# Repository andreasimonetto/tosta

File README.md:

# Tosta

Tosta is a **low-power terminal interface module** built around the [STM32G030](docs/STM32G0x0.pdf) microcontroller. The module features:

- 48x84 monochrome pixel matrix (Nokia 5510 LCD using [PCD8544](docs/PCD8544.pdf) controller)
- configurable dimmable backlight
- configurable display standby timer
- a rotary encoder with central switch
- a D-Pad joystick with central switch
- 4 tactile switches
- a speaker
- an UART interface @ 115200 baud/s
- an I2C slave interface @ 400KHz (address 0x7D)
- 150uA consumption in standby mode

## User guide

The main communication interface (characters based) is UART @ 115200 baud/s.
I2C (binary based) is used for fast display update among other things.

### UART Inputs

When the module receive an input, it send a corresponding command character as
follows:

Event                        | Hex  | Char
---------------------------- | ---- | ----
SW1 pressed                  | 0x41 | A
SW1 released                 | 0x61 | a
SW2 pressed                  | 0x42 | B
SW2 released                 | 0x62 | b
SW3 pressed                  | 0x43 | C
SW3 released                 | 0x63 | c
SW4 pressed                  | 0x44 | D
SW4 released                 | 0x64 | d
D-Pad button pressed         | 0x45 | E
D-Pad button released        | 0x65 | e
D-Pad left pressed           | 0x46 | F
D-Pad left released          | 0x66 | f
D-Pad right pressed          | 0x47 | G
D-Pad right released         | 0x67 | g
D-Pad up pressed             | 0x48 | H
D-Pad up released            | 0x68 | h
D-Pad down pressed           | 0x49 | I
D-Pad down released          | 0x69 | i
Encoder button pressed       | 0x4A | J
Encoder button released      | 0x6A | j
Encoder turn clockwise       | 0x2B | +
Encoder turn anti-clockwise  | 0x2D | -

### Display matrix

The display matrix comprises 84 horizontal by 48 vertical pixels.
Each individual pixel is either *on* (1) or *off* (0) which corresponds to the
status of a single bit. Individual bits are grouped into bytes, representing
a sub-column of 8 pixels.

The next byte is the nearby sub-column, on the right side. The display
frame buffer contains a total 504 bytes: 84 for the upper sub-columns, 84 for
the next ones and so on, for a total of 6 (84x6 bytes, row-major ordering).

Characters are a logical subdivision into a 14x6 matrix, in which each cell is
a 6x8 pixels sub-matrix (see blue lines).

```
h   0x7f 0x08 0x04 0x04 0x78 0x00
e   0x38 0x54 0x54 0x54 0x18 0x00
l   0x00 0x41 0x7f 0x40 0x00 0x00
l   0x00 0x41 0x7f 0x40 0x00 0x00
o   0x38 0x44 0x44 0x44 0x38 0x00
!   0x00 0x00 0x5f 0x00 0x00 0x00
```

### UART outputs

Writing characters works as usual on a *tty* device, using standard ASCII
encoding (printable characters from 0x20 up to 0x7F). There are few special
characters:

- `\a` (bell): play a C4 note from the speaker for 250ms
- `\b` (backspace): delete the last displayed character
- `\n` (line feed): newline
- `\f` (form feed): clear screen
- `\r` (carriage return): move cursor to the beginning of the current line

The user can also add non-standard custom characters (from 0x80 to 0xFF) using
[parametric escape sequences](#escape-sequences).

#### Escape sequences

Escape sequences are used to obtain special behaviours. In order to start
an escape sequence, the special character `\e` (or `\x1B` or `\033`) must be
used.

Basic sequences are:

Sequence | Effect
-------- | ---------------------------------
`\es`    | Put the display in standby
`\ew`    | Wake up the display from standby
`\el`    | Display an awesome logo

Advanced sequences allow passing numerical parameters, and they're started
using `\e[` (i.e. `\x1B[` or `\033[`).

Sequence                           | Effect
-----------------                  | ------------------------------------------------------------
`\e[`N`b`                          | Set display backlight brightness, with *N in [0, 127]*
`\e[`N`,`A`,`B`,`C`,`D`,`E`,`F`c`  | Set user character *N*, specifying bytes in the character sub-matrix from left to right (*N in [128, 255]*; *A,B,C,D,E,F in [0, 255])*
`\e[`F`,`T`p`                      | Play sound (immediate) having frequency *F* for *T* milliseconds
`\e[`F`,`T`q`                      | Enqueue sound playing with frequency *F* for *T* milliseconds
`\e[`T`s`                          | Set the display standby timer in *T* milliseconds (0 to disable standby)
`\e[`X`,`Y`z`                      | Set cursor position to *X in [0, 13]* and *Y in [0, 5]*

##### Example

```sh
stty -F /dev/ttyUSB0 115200
echo -ne "\e[128,12,30,60,30,12,0c" >>/dev/ttyUSB0
echo -ne "\f\x80\x80\x80\x80\x80\x80\x80\x80\x80\x80\x80\x80\x80\x80Frere Jacques\n\x80\x80\x80\x80\x80\x80\x80\x80\x80\x80\x80\x80\x80\x80" >>/dev/ttyUSB0
echo -ne "\e[1047,500q\e[1175,500q\e[1319,500q\e[1047,500q\e[1047,500q\e[1175,500q\e[1319,500q\e[1047,500q\e[1319,500q\e[1397,500q\e[1568,500q\e[0,500q\e[1319,500q\e[1397,500q\e[1568,500q" >>/dev/ttyUSB0
```

### I²C

- Send 1 byte to address 0x7D for command (0), necessary to wake the MCU from stop mode nicely
- Send the framebuffer (504 bytes) to address 0x7D
- ...

## Firmware

Firmware is written using the [STM32 Cube IDE](https://www.st.com/en/development-tools/stm32cubeide.html).

### Peripherals assignment:

- TIM1: speaker PWM
- TIM3: LCD backlight PWM
- TIM14: Inputs debounce
- SPI1+DMA: LCD data output
- UART: main serial communication interface
- I2C1: secondary communication interface (slave)

## Hardware

## Trivia

```C
0x7D == ('t' ^ 'o' ^ 's' ^ 't' ^ 'a')
```

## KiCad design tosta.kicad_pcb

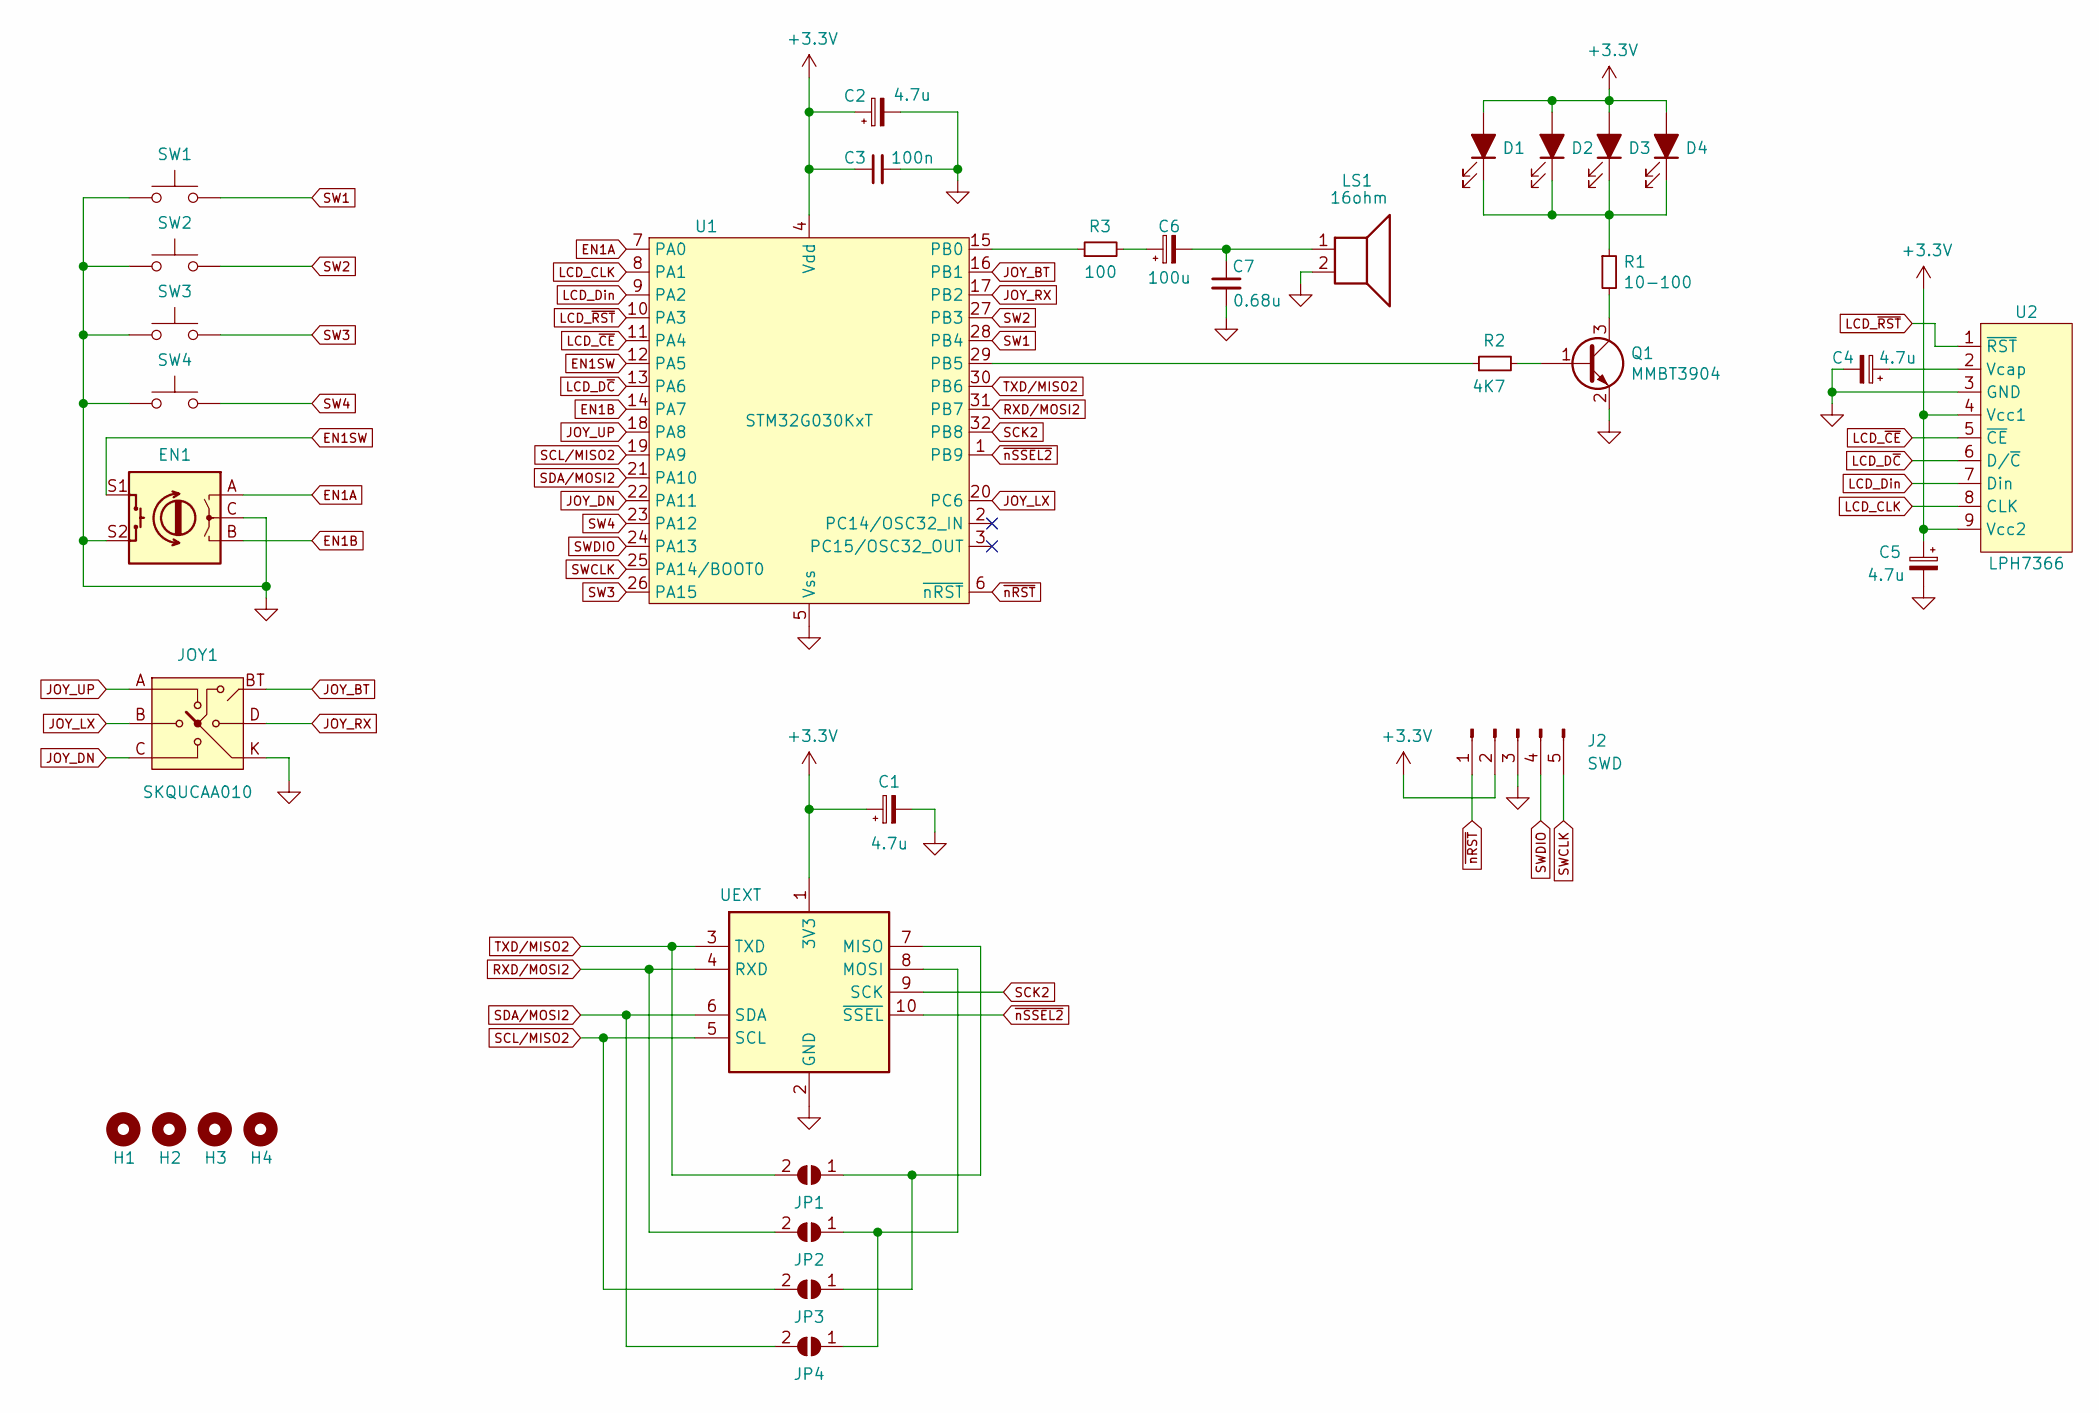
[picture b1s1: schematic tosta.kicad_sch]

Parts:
C1, C2, C4, C5: 4.7u; CP_EIA-3216-12_Kemet-S_Pad1.58x1.35mm_HandSolder
C3: 100n; C_0805_2012Metric_Pad1.15x1.40mm_HandSolder
C6: 100u; CP_EIA-3216-12_Kemet-S_Pad1.58x1.35mm_HandSolder
C7: 0.68u; C_0805_2012Metric_Pad1.18x1.45mm_HandSolder
D1, D2, D3, D4: LED_ALT; LED_0805_2012Metric
EN1: Rotary_Encoder_Switch; RotaryEncoder_Alps_EC12E-Switch_Vertical_H20mm
H1, H2, H3, H4: MountingHole; M3_ISO7380
J2: SWD; PinHeader_1x05_P2.54mm_Vertical
JOY1: SKQUCAA010
JP1, JP2, JP3, JP4: SolderJumper_2_Open; SolderJumper-2_P1.3mm_Open_RoundedPad1.0x1.5mm
LS1: 16ohm; KY_BUZ
Q1: MMBT3904; SOT-23
R1: 10-100; R_0805_2012Metric_Pad1.15x1.40mm_HandSolder
R2: 4K7; R_0805_2012Metric_Pad1.15x1.40mm_HandSolder
R3: 100; R_0805_2012Metric_Pad1.20x1.40mm_HandSolder
SW1, SW2, SW3, SW4: SW_Push; SW_PUSH_6mm_H4.3mm
U1: STM32G030KxT; LQFP-32_7x7mm_P0.8mm
U2: LPH7366
UEXT: UEXT; IDC-Header_2x05_P2.54mm_Vertical

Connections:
+3V3: C1.1, C2.1, C3.1, C5.1, D1.2 (A), D2.2 (A), D3.2 (A), D4.2 (A), J2.2, U1.4 (Vdd), U2.4 (Vcc1), U2.9 (Vcc2), UEXT.1 (3V3)
EN1A: EN1.A, U1.7 (PA0)
EN1B: EN1.B, U1.14 (PA7)
EN1SW: EN1.S1, U1.12 (PA5)
GND: C1.2, C2.2, C3.2, C4.2, C5.2, C7.2, EN1.C, EN1.S2, J2.3, JOY1.K, LS1.2, Q1.2 (E), SW1.2, SW2.2, SW3.2, SW4.2, U1.5 (Vss), U2.3 (GND), UEXT.2 (GND)
JOY_BT: JOY1.BT, U1.16 (PB1)
JOY_DN: JOY1.C, U1.22 (PA11)
JOY_LX: JOY1.B, U1.20 (PC6)
JOY_RX: JOY1.D, U1.17 (PB2)
JOY_UP: JOY1.A, U1.18 (PA8)
LCD_CLK: U1.8 (PA1), U2.8 (CLK)
LCD_Din: U1.9 (PA2), U2.7 (Din)
LCD_D~C: U1.13 (PA6), U2.6 (D/~C)
LCD_~CE: U1.11 (PA4), U2.5 (~CE)
LCD_~RST: U1.10 (PA3), U2.1 (~RST)
unnamed: C4.1, U2.2 (Vcap)
unnamed: C6.1, R3.2
unnamed: C6.2, C7.1, LS1.1
unnamed: D1.1 (K), D2.1 (K), D3.1 (K), D4.1 (K), R1.1
unnamed: JP1.1 (A), JP3.1 (A), UEXT.7 (MISO)
unnamed: JP2.1 (A), JP4.1 (A), UEXT.8 (MOSI)
unnamed: Q1.1 (B), R2.2
unnamed: Q1.3 (C), R1.2
unnamed: R2.1, U1.29 (PB5)
unnamed: R3.1, U1.15 (PB0)
RXD/MOSI2: JP2.2 (B), U1.31 (PB7), UEXT.4 (RXD)
SCK2: U1.32 (PB8), UEXT.9 (SCK)
SCL/MISO2: JP3.2 (B), U1.19 (PA9), UEXT.5 (SCL)
SDA/MOSI2: JP4.2 (B), U1.21 (PA10), UEXT.6 (SDA)
SW1: SW1.1, U1.28 (PB4)
SW2: SW2.1, U1.27 (PB3)
SW3: SW3.1, U1.26 (PA15)
SW4: SW4.1, U1.23 (PA12)
SWCLK: J2.5, U1.25 (PA14/BOOT0)
SWDIO: J2.4, U1.24 (PA13)
TXD/MISO2: JP1.2 (B), U1.30 (PB6), UEXT.3 (TXD)
~nRST: J2.1, U1.6 (~nRST)
~nSSEL2: U1.1 (PB9), UEXT.10 (~SSEL)

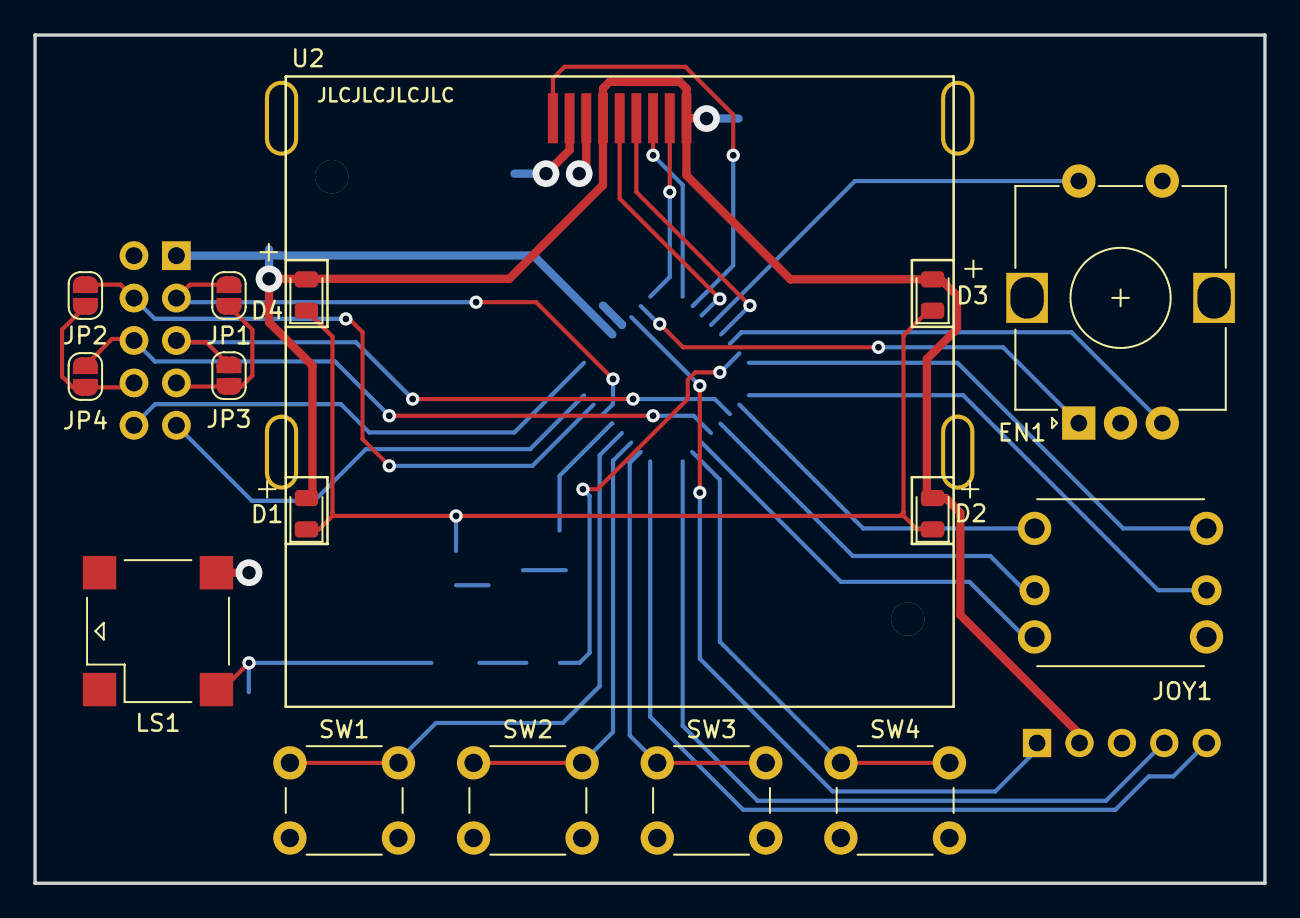
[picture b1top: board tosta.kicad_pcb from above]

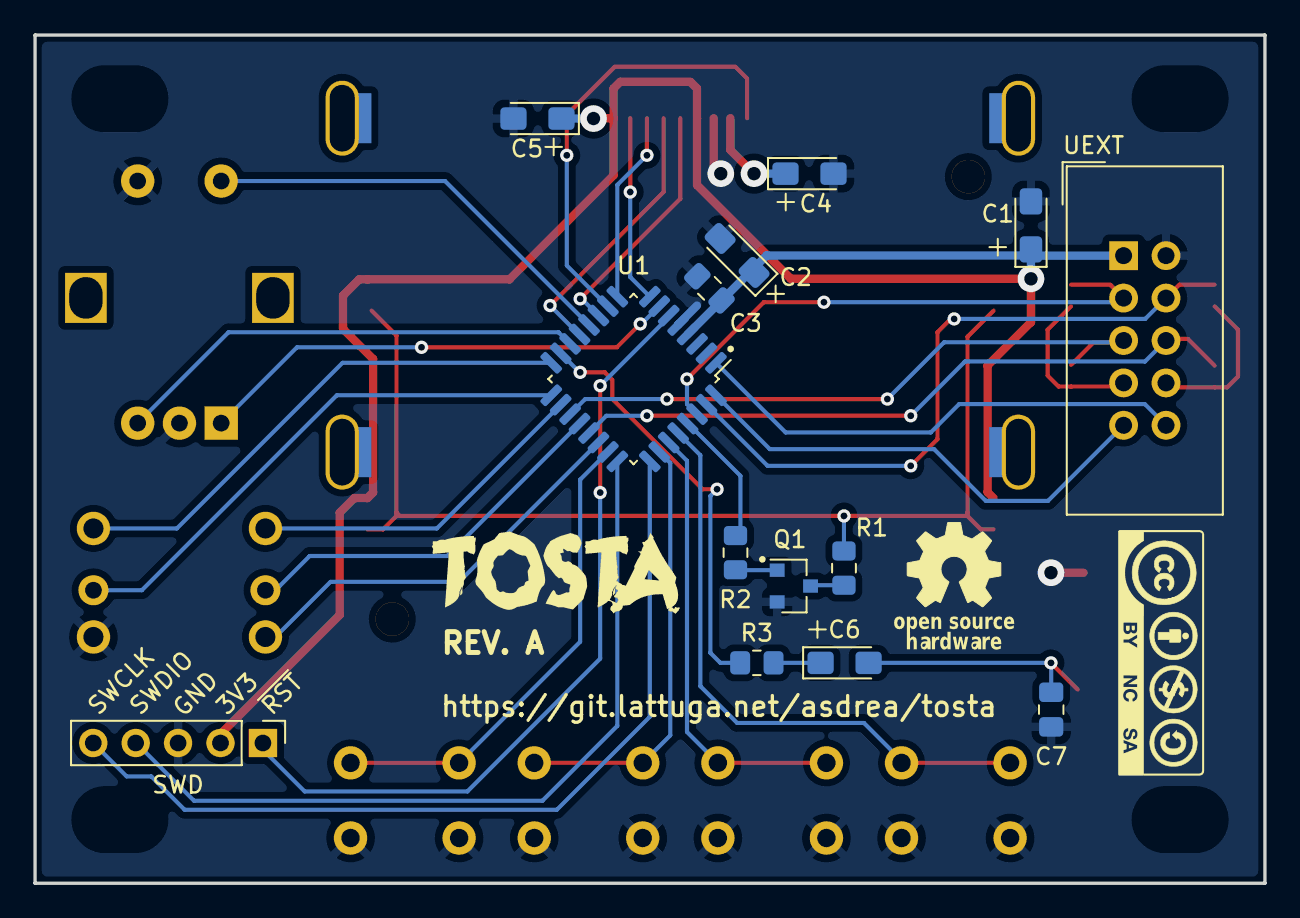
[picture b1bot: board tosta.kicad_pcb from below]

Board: 2 copper layers, 73.7 x 50.8 mm, 37 parts (17 on the bottom side), 38 nets.

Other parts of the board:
CC_BYNCSA: G***; cc_byncsa
OSHW: G***; oshw
svg2mod: G***; logo

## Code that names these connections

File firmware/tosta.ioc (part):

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Mcu.Name=STM32G030K(6-8)Tx
Mcu.Package=LQFP32
Mcu.UserName=STM32G030K6Tx
PA0.GPIOParameters=GPIO_PuPd,GPIO_Label,GPIO_ModeDefaultEXTI
PA0.GPIO_Label=EN1A
PA0.GPIO_ModeDefaultEXTI=GPIO_MODE_IT_RISING_FALLING
PA0.GPIO_PuPd=GPIO_PULLUP
PA0.Signal=GPXTI0
PA1.GPIOParameters=GPIO_Speed,GPIO_Label
PA1.GPIO_Label=LCD_CLK
PA1.GPIO_Speed=GPIO_SPEED_FREQ_HIGH
PA1.Mode=TX_Only_Simplex_Unidirect_Master
PA1.Signal=SPI1_SCK
PA10.GPIOParameters=GPIO_PuPdOD,GPIO_Label
PA10.GPIO_Label=SDA
PA10.GPIO_PuPdOD=GPIO_NOPULL
PA10.Mode=I2C
PA10.Signal=I2C1_SDA
PA11\ [PA9].GPIOParameters=GPIO_PuPd,GPIO_Label,GPIO_ModeDefaultEXTI
PA11\ [PA9].GPIO_Label=JOY_DN
PA11\ [PA9].GPIO_ModeDefaultEXTI=GPIO_MODE_IT_RISING_FALLING
PA11\ [PA9].GPIO_PuPd=GPIO_PULLUP
PA11\ [PA9].Signal=GPXTI11
PA12\ [PA10].GPIOParameters=GPIO_PuPd,GPIO_Label,GPIO_ModeDefaultEXTI
PA12\ [PA10].GPIO_Label=SW4
PA12\ [PA10].GPIO_ModeDefaultEXTI=GPIO_MODE_IT_RISING_FALLING
PA12\ [PA10].GPIO_PuPd=GPIO_PULLUP
PA12\ [PA10].Signal=GPXTI12
PA13.Mode=Serial_Wire
PA13.Signal=SYS_SWDIO
PA14-BOOT0.Mode=Serial_Wire
PA14-BOOT0.Signal=SYS_SWCLK
PA15.GPIOParameters=GPIO_PuPd,GPIO_Label,GPIO_ModeDefaultEXTI
PA15.GPIO_Label=SW3
PA15.GPIO_ModeDefaultEXTI=GPIO_MODE_IT_RISING_FALLING
PA15.GPIO_PuPd=GPIO_PULLUP
PA15.Signal=GPXTI15
PA2.GPIOParameters=GPIO_Speed,GPIO_Label
PA2.GPIO_Label=LCD_Din
PA2.GPIO_Speed=GPIO_SPEED_FREQ_HIGH
PA2.Mode=TX_Only_Simplex_Unidirect_Master
PA2.Signal=SPI1_MOSI
PA3.GPIOParameters=PinState,GPIO_Label
PA3.GPIO_Label=LCD_nRST
PA3.PinState=GPIO_PIN_SET
PA3.Signal=GPIO_Output
PA4.GPIOParameters=GPIO_Speed,PinState,GPIO_Label
PA4.GPIO_Label=LCD_nCE
PA4.GPIO_Speed=GPIO_SPEED_FREQ_HIGH
PA4.Mode=NSS_Signal_Hard_Output
PA4.PinState=GPIO_PIN_SET
PA4.Signal=SPI1_NSS
PA5.GPIOParameters=GPIO_PuPd,GPIO_Label,GPIO_ModeDefaultEXTI
PA5.GPIO_Label=EN1SW
PA5.GPIO_ModeDefaultEXTI=GPIO_MODE_IT_RISING_FALLING
PA5.GPIO_PuPd=GPIO_PULLUP
PA5.Signal=GPXTI5
PA6.GPIOParameters=GPIO_Label
PA6.GPIO_Label=LCD_DC
PA6.Signal=GPIO_Output
PA7.GPIOParameters=GPIO_PuPd,GPIO_Label,GPIO_ModeDefaultEXTI
PA7.GPIO_Label=EN1B
PA7.GPIO_ModeDefaultEXTI=GPIO_MODE_IT_RISING_FALLING
PA7.GPIO_PuPd=GPIO_PULLUP
PA7.Signal=GPXTI7
PA8.GPIOParameters=GPIO_PuPd,GPIO_Label,GPIO_ModeDefaultEXTI
PA8.GPIO_Label=JOY_UP
PA8.GPIO_ModeDefaultEXTI=GPIO_MODE_IT_RISING_FALLING
PA8.GPIO_PuPd=GPIO_PULLUP
PA8.Signal=GPXTI8
PA9.GPIOParameters=GPIO_PuPdOD,GPIO_Label
PA9.GPIO_Label=SCL
PA9.GPIO_PuPdOD=GPIO_NOPULL
PA9.Mode=I2C
PA9.Signal=I2C1_SCL
PB0.GPIOParameters=GPIO_Label
PB0.GPIO_Label=SPKR
PB0.Mode=PWM Generation2 CH2N
PB0.Signal=TIM1_CH2N
PB1.GPIOParameters=GPIO_PuPd,GPIO_Label,GPIO_ModeDefaultEXTI
PB1.GPIO_Label=JOY_BT
PB1.GPIO_ModeDefaultEXTI=GPIO_MODE_IT_RISING_FALLING
PB1.GPIO_PuPd=GPIO_PULLUP
PB1.Signal=GPXTI1
PB2.GPIOParameters=GPIO_PuPd,GPIO_Label,GPIO_ModeDefaultEXTI
PB2.GPIO_Label=JOY_RX
PB2.GPIO_ModeDefaultEXTI=GPIO_MODE_IT_RISING_FALLING
PB2.GPIO_PuPd=GPIO_PULLUP
PB2.Signal=GPXTI2
PB3.GPIOParameters=GPIO_PuPd,GPIO_Label,GPIO_ModeDefaultEXTI
PB3.GPIO_Label=SW2
PB3.GPIO_ModeDefaultEXTI=GPIO_MODE_IT_RISING_FALLING
PB3.GPIO_PuPd=GPIO_PULLUP
PB3.Signal=GPXTI3
PB4.GPIOParameters=GPIO_PuPd,GPIO_Label,GPIO_ModeDefaultEXTI
PB4.GPIO_Label=SW1
PB4.GPIO_ModeDefaultEXTI=GPIO_MODE_IT_RISING_FALLING
PB4.GPIO_PuPd=GPIO_PULLUP
PB4.Signal=GPXTI4
PB5.GPIOParameters=GPIO_ModeDefaultPP,GPIO_Label
PB5.GPIO_Label=LCD_BL
PB5.GPIO_ModeDefaultPP=GPIO_MODE_AF_PP
PB5.Signal=S_TIM3_CH2
PB6.Mode=Asynchronous
PB6.Signal=USART1_TX
PB7.Mode=Asynchronous
PB7.Signal=USART1_RX
PB8.Signal=SPI2_SCK
PB9.GPIOParameters=GPIO_Label
PB9.GPIO_Label=nSSEL
PB9.Signal=SPI2_NSS
PC14-OSC32_IN\ (PC14).Signal=GPIO_Output
PC15-OSC32_OUT\ (PC15).Signal=GPIO_Output
PC6.GPIOParameters=GPIO_PuPd,GPIO_Label,GPIO_ModeDefaultEXTI
PC6.GPIO_Label=JOY_LX
PC6.GPIO_ModeDefaultEXTI=GPIO_MODE_IT_RISING_FALLING
PC6.GPIO_PuPd=GPIO_PULLUP
PC6.Signal=GPXTI6
RCC.HSE_VALUE=8000000
RCC.SYSCLKFreq_VALUE=16000000
board=custom

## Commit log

2020-06-03 Repo initialized
2020-11-26 Added SWD header
2020-11-29 Updated speaker driver
2021-01-22 Basic peripherals and UART firmware
2021-01-24 Added basic I2C
2021-01-24 Fixed README typo
2021-01-24 Imported design files
2021-01-31 I2C off by default
2021-02-02 Optimized LCD Vop parameter
